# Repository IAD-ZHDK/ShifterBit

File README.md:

# Shifter Bit

**A [littleBits](http://littlebits.cc) compatible module that connects to [shiftr.io](https://shiftr.io).**

## Parts

- [ESP8266 Breakout](http://www.mouser.ch/ProductDetail/Adafruit/2471/?qs=sGAEpiMZZMuJ3l9lTgMBp%2frnoxsPagxMQVIxc1X%252bEHbnrRJkxRVMMQ%3d%3d)
- [SD Card Holder](http://www.mouser.ch/ProductDetail/Molex/47352-1001/?qs=sGAEpiMZZMuJakaoiLiBpqoYXsE4YrD3r%2fU0grh%2fJ8Q%3d)
- [MCP41010](http://ww1.microchip.com/downloads/en/DeviceDoc/11195c.pdf)
- SD Card & Adapter

## Useful Links

- [Little Bits Eagle Templates](https://github.com/littleBitsbitLab/HDK-eagle-templates-libraries)
- [SD Card Holder Eagle Part](http://www.eaglecentral.ca/forums/index.php?t=msg&th=48291&start=0&e7001add2d4226236598bac9739173f3)
- [ESP8266 Breakout Info](https://learn.adafruit.com/adafruit-huzzah-esp8266-breakout/overview)

## Configuration

To configure the bit, edit the `/config.txt` on the SD card:

```
# Wifi Config
wifi_ssid: MY_WIFI
wifi_key: hidden_secret

# MQTT Config
mqtt_broker: broker.shiftr.io
mqtt_user: try
mqtt_password: try
mqtt_client_id: bit1

# Publish & Subscribe
# set to '-' to disable
publish_topic: data
subscribe_topic: -

# Uncomment to enable JSON
# use_json
```

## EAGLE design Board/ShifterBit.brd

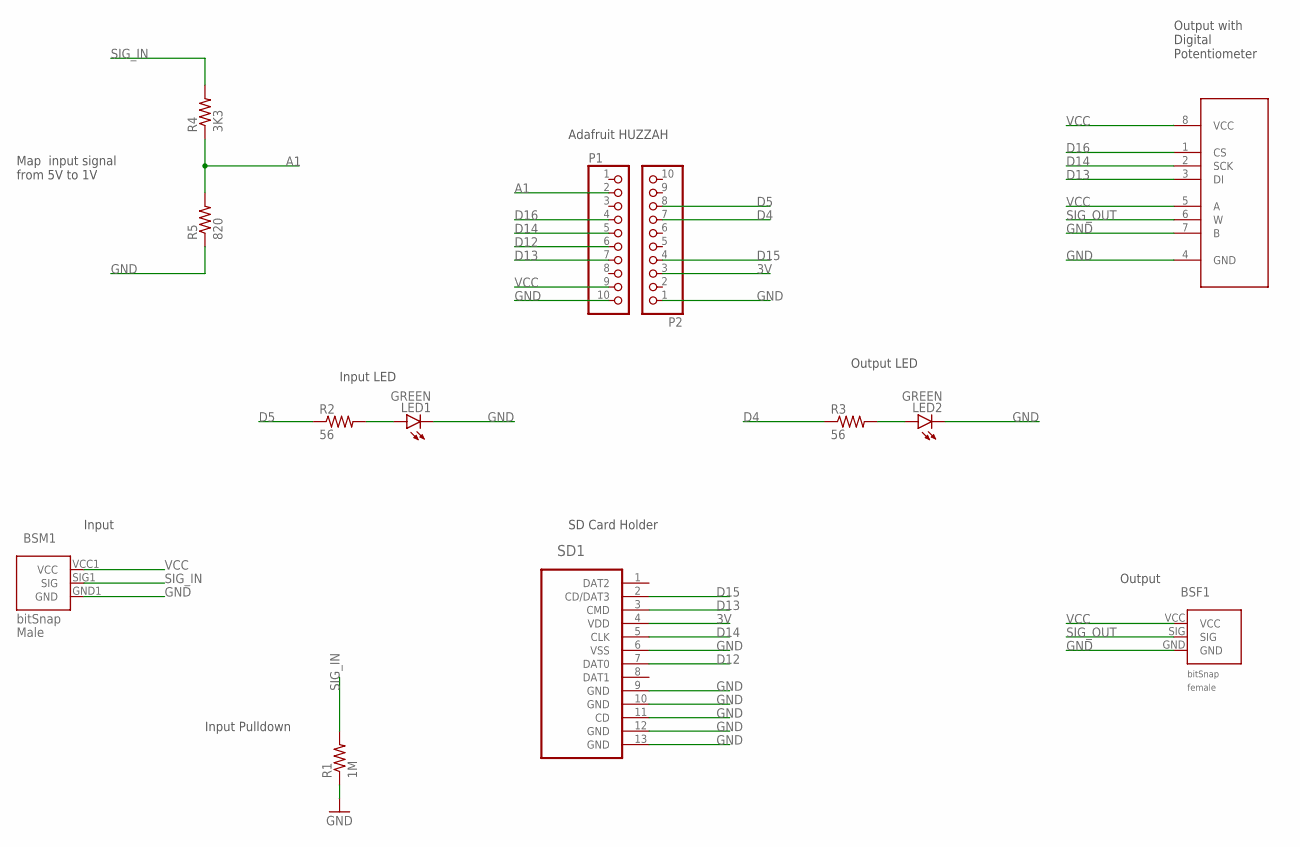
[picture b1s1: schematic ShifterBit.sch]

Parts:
BSF1: BITSNAP_V03_FEMALE
BSM1: BITSNAP_V03_MALE
DPOT1: MCP41XXX; SO08
LED1, LED2: GREEN; LED-1206
P1, P2: PINHD-1X10; 1X10-BIG
R1: 1M; RES-1206
R2, R3: 56; 1206
R4: 3K3; 1206
R5: 820; 1206
SD1: HIROSE_DM3CS-SF

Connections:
3V: P2.3, SD1.4 (VDD)
A1: P1.2, R4.1, R5.2
D4: P2.7, R3.1
D5: P2.8, R2.1
D12: P1.6, SD1.7 (DAT0)
D13: DPOT1.3 (DI), P1.7, SD1.3 (CMD)
D14: DPOT1.2 (SCK), P1.5, SD1.5 (CLK)
D15: P2.4, SD1.2 (CD/DAT3)
D16: DPOT1.1 (CS), P1.4
GND: BSF1.GND, BSM1.GND1 (GND), DPOT1.4 (GND), DPOT1.7 (B), LED1.C, LED2.C, P1.10, P2.1, R1.1, R5.1, SD1.6 (VSS), SD1.9 (GND), SD1.10 (GND), SD1.11 (CD), SD1.12 (GND), SD1.13 (GND)
unnamed: LED1.A, R2.2
unnamed: LED2.A, R3.2
SIG_IN: BSM1.SIG1 (SIG), R1.2, R4.2
SIG_OUT: BSF1.SIG, DPOT1.6 (W)
VCC: BSF1.VCC, BSM1.VCC1 (VCC), DPOT1.5 (A), DPOT1.8 (VCC), P1.9

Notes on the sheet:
Map input signal from 5V to 1V
Input LED
Output LED
Input Pulldown
Adafruit HUZZAH
SD Card Holder
Input
Output
Output with Digital Potentiometer

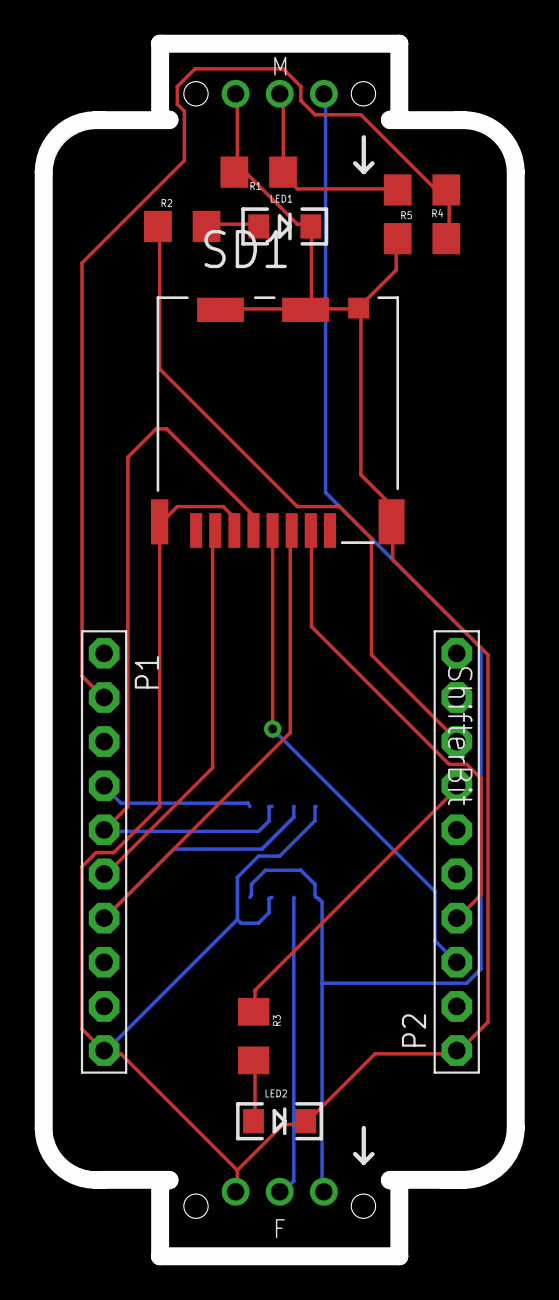
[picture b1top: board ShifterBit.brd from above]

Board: 2 copper layers, 27.2 x 69.8 mm, 13 parts (1 on the bottom side), 15 nets.

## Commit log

2015-09-16 added Arduino test code
2015-09-17 added link to sd card holder
2015-09-17 added first board layout test
2015-09-18 added resources
2015-09-18 updated config layout
2015-09-18 added basic esp code
2015-09-18 removed esd protection
2015-09-20 added nets and leds
2015-09-21 renamed
2015-09-21 fix ignore flag
2015-09-21 use config
2015-09-21 added interface and display
2015-09-21 obsolete
2015-09-21 renamed and added voltage divider for signal input
2015-09-22 added transistor and some labels
2015-09-22 moved
2015-09-22 updated interface and display stuff
2015-09-22 fix value
2015-09-22 added resistor to dac
2015-09-26 try to connect forever
2015-09-26 added input smoothing
2015-09-26 reduce input by 1
2015-09-26 added micro sd pinout
2015-09-26 write low when v == 0
2015-09-26 connected the sd card
2015-09-26 changed resistor name
2015-09-27 fix pwm stuff
2015-09-27 setup and read in one function
2015-09-27 added component to board
2015-09-27 made board longer and placed all components on top
2015-09-27 better placement
2015-09-27 prepared digi pot SPi
2015-09-30 fix some restarts
2015-09-30 constrain input
2015-09-30 write value using digi pot
2015-09-30 ignore auto router stuff
2015-09-30 corrected milling path
2015-09-30 corrected socket position
2015-09-30 added some aesthetics
2015-09-30 renamed signal
2015-09-30 removed unused nets
2015-09-30 repositioned elements
2015-09-30 ignore pdfs
2015-09-30 load sparkfun design rules and auto route
2015-09-30 grounded cd
2015-09-30 use 1206 packages
2015-10-01 added parts list
2015-10-06 updated orders
2015-10-09 fixed missing connection
2015-10-09 switched pins
2015-10-09 added sample config
2015-10-11 update client id
2016-04-14 reorganized to make compilable again
2018-04-06 added missing callback config
2018-04-06 added json support

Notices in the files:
parts and their libraries:
SparkFun-LED: Licensing: Creative Commons ShareAlike 4.0 International - https://creativecommons.org/licenses/by-sa/4.0
